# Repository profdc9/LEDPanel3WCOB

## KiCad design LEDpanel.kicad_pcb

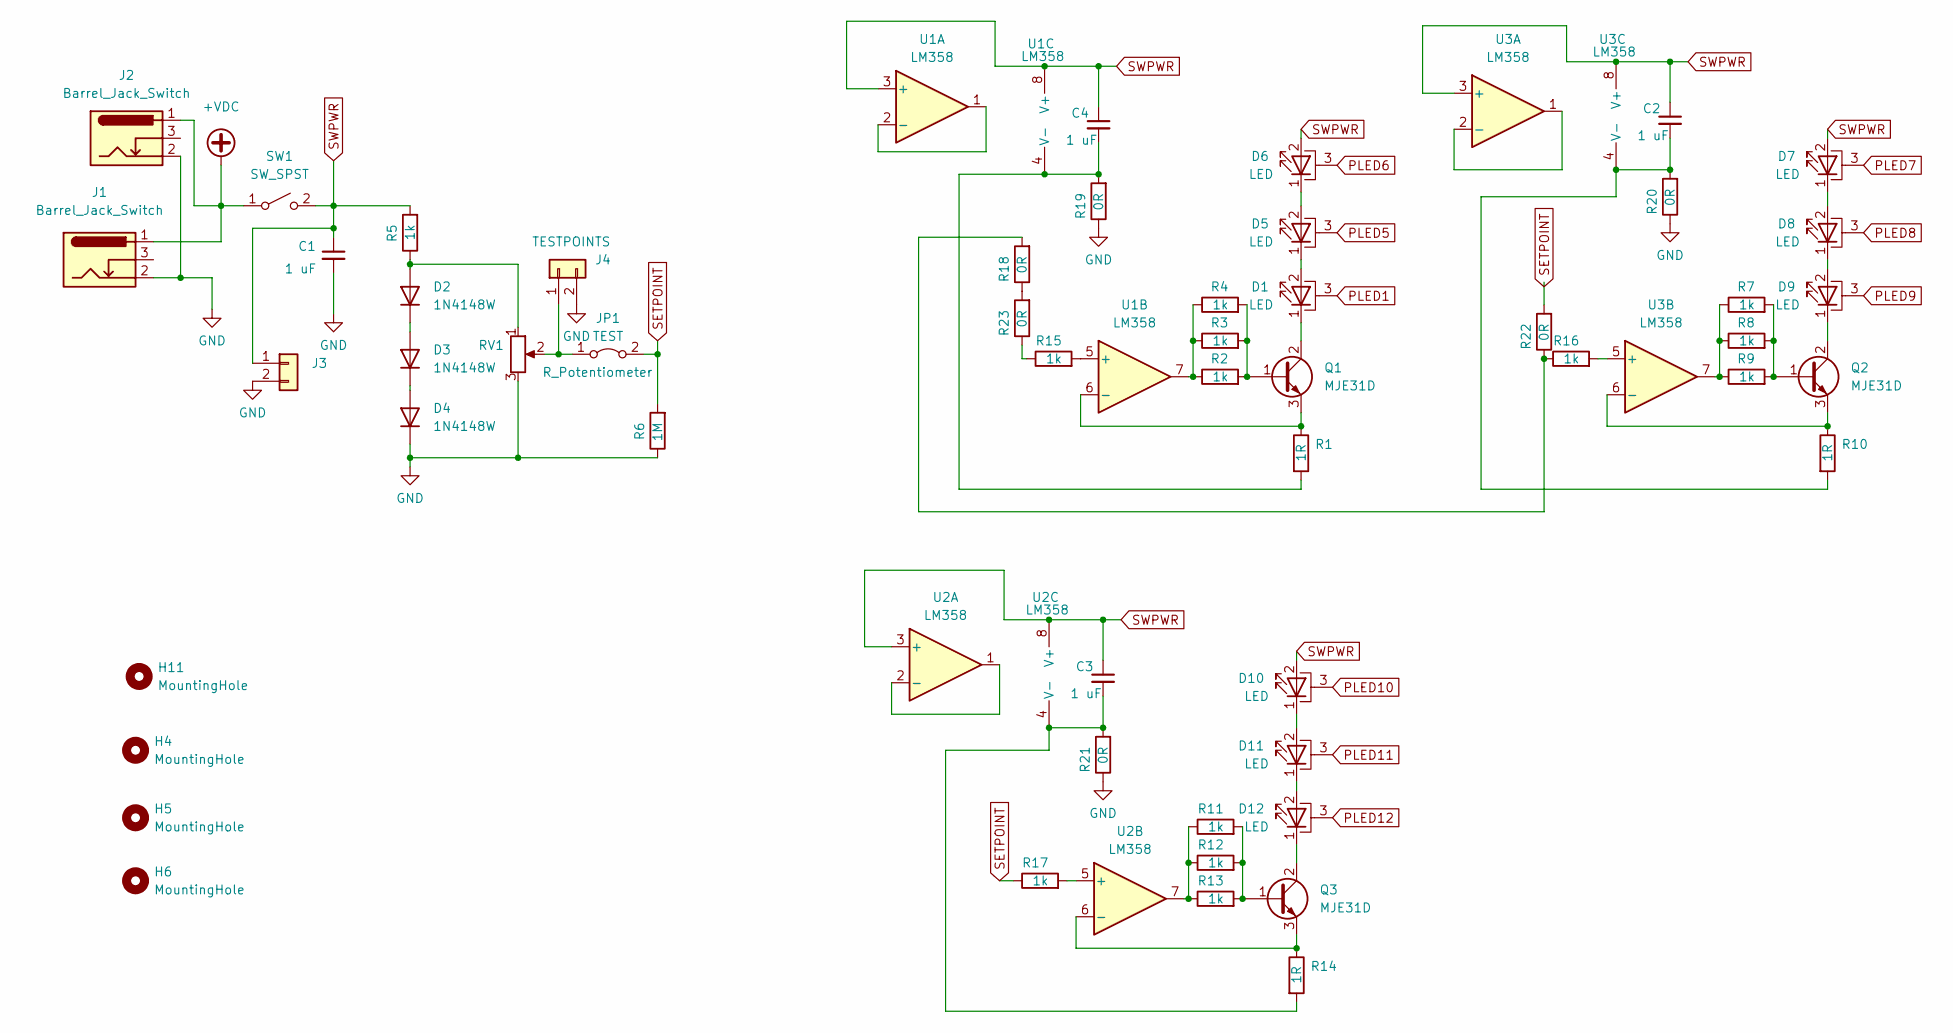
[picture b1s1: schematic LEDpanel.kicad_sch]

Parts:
C1, C2, C3, C4: 1 uF; C_0805_2012Metric_Pad1.18x1.45mm_HandSolder; LCSC C28323
D1, D5, D6, D7, D8, D9, D10, D11, D12: LED; LED_1W_3W_R8
D2, D3, D4: 1N4148W; D_SOD-123; LCSC C81598
H4, H5, H6, H11: MountingHole; MountingHole_4mm
J1, J2: Barrel_Jack_Switch; BarrelJack_Horizontal
J3: Conn_01x02; TerminalBlock_Phoenix_MKDS-1,5-2-5.08_1x02_P5.08mm_Horizont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
J4: TESTPOINTS; PinHeader_1x02_P2.54mm_Vertical
JP1: TEST; PinHeader_1x02_P2.54mm_Vertical
Q1, Q2, Q3: MJE31D; TO-252-3_TabPin2; LCSC C27596
R1, R10, R14: 1R; R_2512_6332Metric_Pad1.40x3.35mm_HandSolder; LCSC C876259
R2, R3, R4, R5, R7, R8, R9, R11, R12, R13, R15, R16, R17: 1k; R_1206_3216Metric_Pad1.30x1.75mm_HandSolder; LCSC C4410
R6: 1M; R_0805_2012Metric_Pad1.20x1.40mm_HandSolder; LCSC C17514
R18, R19, R20, R21, R22, R23: 0R; R_1206_3216Metric_Pad1.30x1.75mm_HandSolder; LCSC C17888
RV1: R_Potentiometer; Potentiometer_Bourns_3296W_Vertical
SW1: SW_SPST; TerminalBlock_Phoenix_MKDS-1,5-2-5.08_1x02_P5.08mm_Horizont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
U1, U2, U3: LM358; SOIC-8_3.9x4.9mm_P1.27mm; LCSC C7950

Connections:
+VDC: J1.1, J2.1, SW1.1 (A)
GND: C1.2, D4.1 (K), J1.2, J2.2, J3.2, J4.2, R6.1, R19.1, R20.1, R21.1, RV1.3
unnamed: D1.2 (A), D5.1 (K)
unnamed: D1.1 (K), Q1.2 (C)
unnamed: D2.2 (A), R5.1, RV1.1
unnamed: D2.1 (K), D3.2 (A)
unnamed: D3.1 (K), D4.2 (A)
unnamed: D5.2 (A), D6.1 (K)
unnamed: D7.1 (K), D8.2 (A)
unnamed: D8.1 (K), D9.2 (A)
unnamed: D9.1 (K), Q2.2 (C)
unnamed: D10.1 (K), D11.2 (A)
unnamed: D11.1 (K), D12.2 (A)
unnamed: D12.1 (K), Q3.2 (C)
unnamed: J4.1, JP1.1 (A), RV1.2
unnamed: Q1.1 (B), R2.2, R3.2, R4.2
unnamed: Q1.3 (E), R1.1, U1.6 (-)
unnamed: Q2.1 (B), R7.2, R8.2, R9.2
unnamed: Q2.3 (E), R10.1, U3.6 (-)
unnamed: Q3.1 (B), R11.2, R12.2, R13.2
unnamed: Q3.3 (E), R14.1, U2.6 (-)
unnamed: R2.1, R3.1, R4.1, U1.7
unnamed: R7.1, R8.1, R9.1, U3.7
unnamed: R11.1, R12.1, R13.1, U2.7
unnamed: R15.1, R23.1
unnamed: R16.1, R18.2, R22.1
unnamed: R18.1, R23.2
unnamed: U1.1, U1.2 (-)
unnamed: R15.2, U1.5 (+)
unnamed: C4.2, R1.2, R19.2, U1.4 (V-)
unnamed: U2.1, U2.2 (-)
unnamed: R17.2, U2.5 (+)
unnamed: C3.2, R14.2, R21.2, U2.4 (V-)
unnamed: U3.1, U3.2 (-)
unnamed: R16.2, U3.5 (+)
unnamed: C2.2, R10.2, R20.2, U3.4 (V-)
PLED1: D1.3 (PAD)
PLED5: D5.3 (PAD)
PLED6: D6.3 (PAD)
PLED7: D7.3 (PAD)
PLED8: D8.3 (PAD)
PLED9: D9.3 (PAD)
PLED10: D10.3 (PAD)
PLED11: D11.3 (PAD)
PLED12: D12.3 (PAD)
SETPOINT: JP1.2 (B), R6.2, R17.1, R22.2
SWPWR: C1.1, C2.1, C3.1, C4.1, D6.2 (A), D7.2 (A), D10.2 (A), J3.1, R5.2, SW1.2 (B), U1.3 (+), U1.8 (V+), U2.3 (+), U2.8 (V+), U3.3 (+), U3.8 (V+)

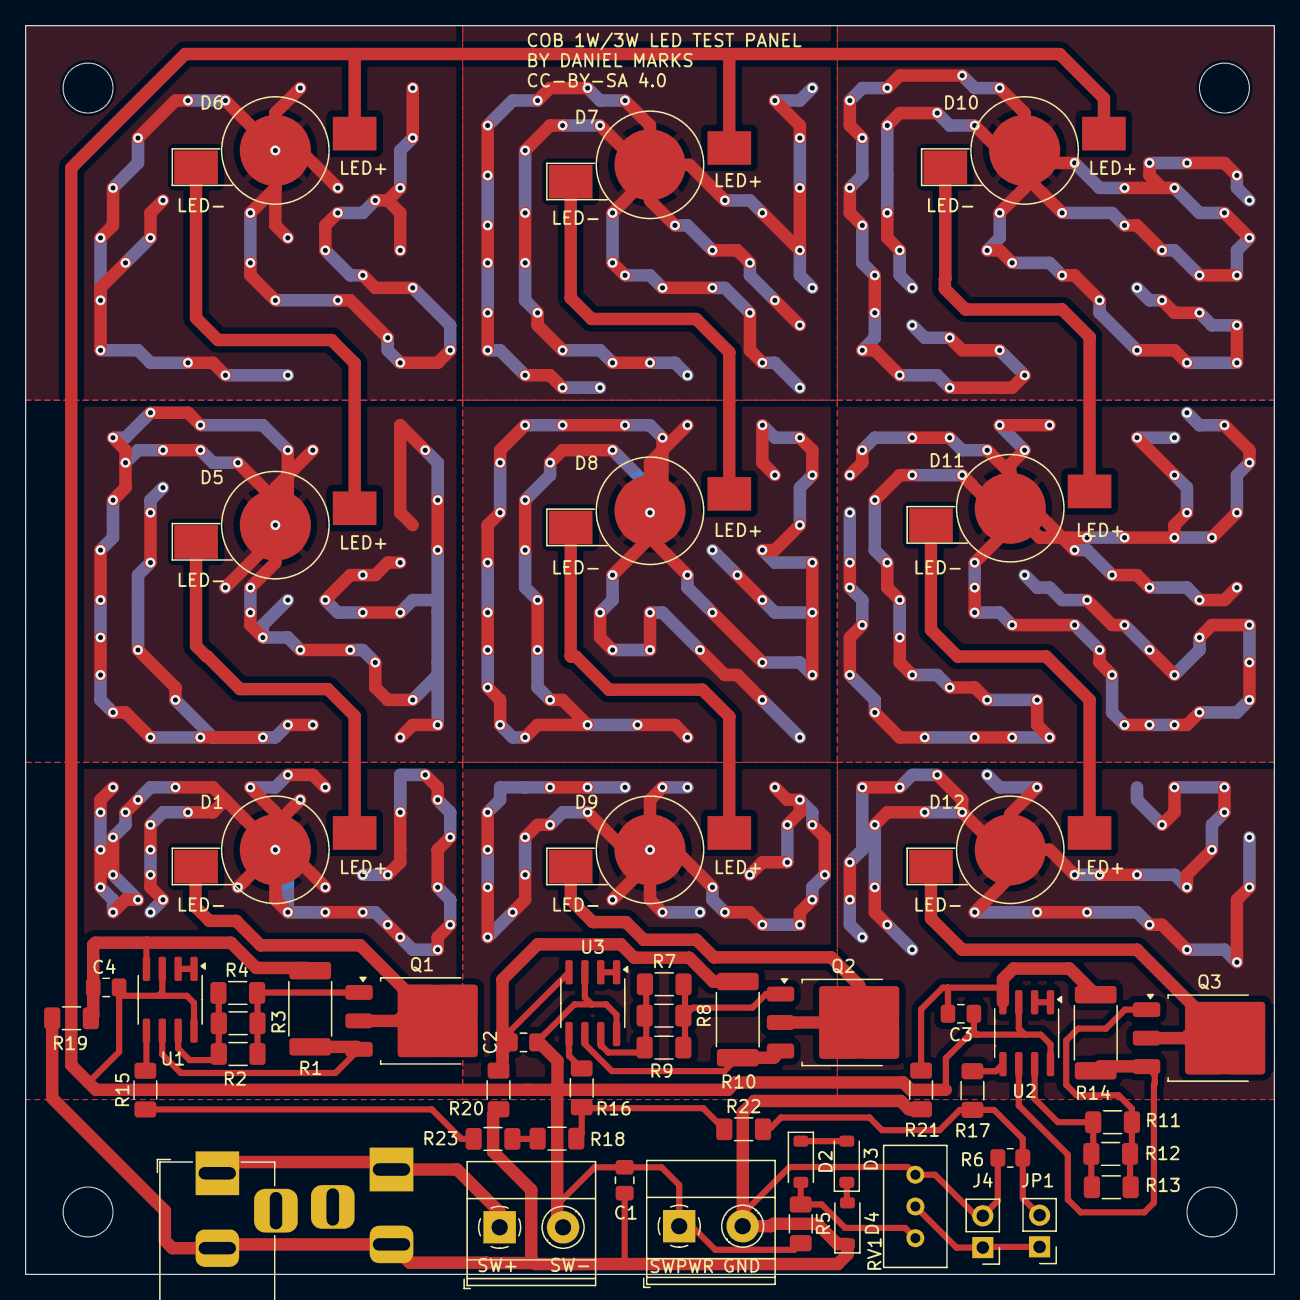
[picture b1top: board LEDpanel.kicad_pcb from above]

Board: 2 copper layers, 100.0 x 100.0 mm, 56 parts (1 on the bottom side), 38 nets.

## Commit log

2025-09-06 Send to JLCPCB

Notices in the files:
LEDpanel.kicad_pcb:
CC-BY-SA 4.0
